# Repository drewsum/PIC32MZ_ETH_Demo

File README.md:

# PIC32MZ_ETH_Demo
A DIY dev board for PIC32MZ EF Ethernet Development

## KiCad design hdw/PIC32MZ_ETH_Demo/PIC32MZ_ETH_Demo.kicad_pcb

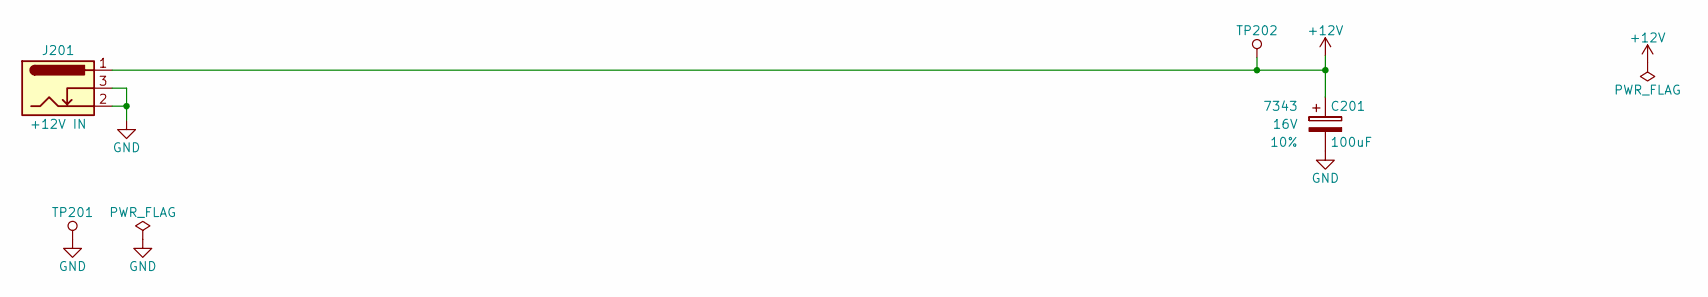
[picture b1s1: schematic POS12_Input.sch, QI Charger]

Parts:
C201: 100uF; CP_Tantalum_Case-X_EIA-7343-43_Reflow; Voltage 16V; Tolerance 10%; Digi-Key PN 718-1102-1-ND
J201: +12V IN; BARREL_JACK
TP201: TP; Pin_Header_Angled_1x01_Pitch2.54mm
TP202: TP; Test_Point

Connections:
+12V: C201.1, J201.1, TP202.1; also elsewhere on the board
GND: C201.2, J201.2, J201.3, TP201.1; also elsewhere on the board

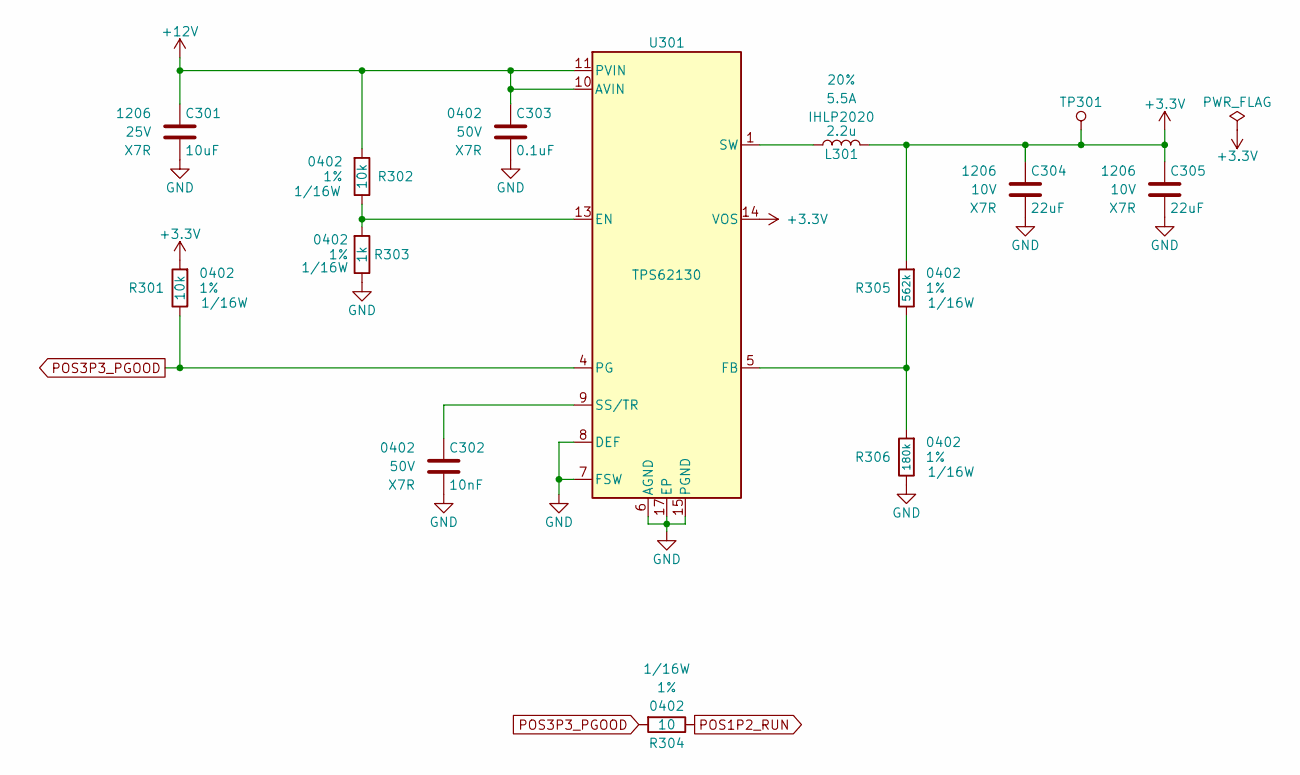
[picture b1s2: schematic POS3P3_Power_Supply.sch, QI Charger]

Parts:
C301: 10uF; C_1206; Voltage 25V; Digi-Key PN 1276-7031-1-ND
C302: 10nF; C_0402; Voltage 50V; Digi-Key PN 490-13295-1-ND
C303: 0.1uF; C_0402; Voltage 50V; Digi-Key PN 490-10701-1-ND
C304, C305: 22uF; C_1206; Voltage 10V; Digi-Key PN 1276-3148-1-ND
L301: 2.2u; L_Vishay_IHLP-2020; Tolerance 20%; Digi-Key PN 541-1236-1-ND
R301, R302: 10k; R_0402; Tolerance 1%; Digi-Key PN RMCF0402FT10K0CT-ND
R303: 1k; R_0402; Tolerance 1%; Digi-Key PN 541-1.00KLCT-ND
R304: 10; R_0402; Tolerance 1%; Digi-Key PN 541-3964-1-ND
R305: 562k; R_0402; Tolerance 1%; Digi-Key PN 541-562KLCT-ND
R306: 180k; R_0402; Tolerance 1%; Digi-Key PN 541-180KLCT-ND
TP301: TP; Test_Point
U301: TPS62130; QFN-16-1EP_3x3mm_Pitch0.5mm; Digi-Key PN 296-37878-1-ND

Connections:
+3V3: C304.1, C305.1, L301.2, R301.1, R305.1, TP301.1, U301.14 (VOS); also elsewhere on the board
+12V: C301.1, C303.1, R302.1, U301.10 (AVIN), U301.11 (PVIN), U301.12 (PVIN); also elsewhere on the board
GND: C301.2, C302.2, C303.2, C304.2, C305.2, R303.2, R306.2, U301.6 (AGND), U301.7 (FSW), U301.8 (DEF), U301.15 (PGND), U301.16 (PGND), U301.17 (EP); also elsewhere on the board
unnamed: C302.1, U301.9 (SS/TR)
unnamed: L301.1, U301.1 (SW), U301.2 (SW), U301.3 (SW)
unnamed: R302.2, R303.1, U301.13 (EN)
unnamed: R305.2, R306.1, U301.5 (FB)
POS1P2_RUN: R304.2; also elsewhere on the board
POS3P3_PGOOD: R301.2, R304.1, U301.4 (PG); also elsewhere on the board

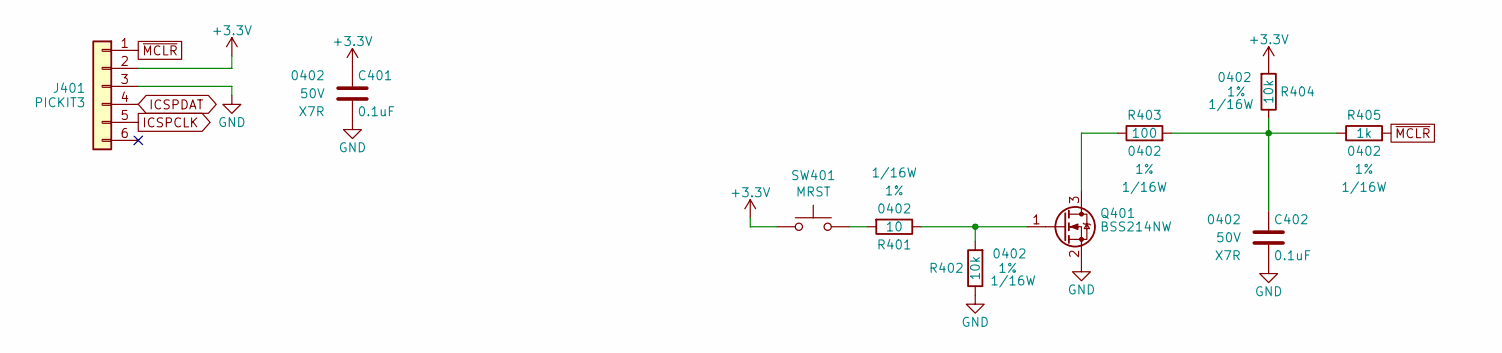
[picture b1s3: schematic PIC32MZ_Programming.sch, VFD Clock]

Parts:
C401, C402: 0.1uF; C_0402; Voltage 50V; Digi-Key PN 490-10701-1-ND
J401: PICKIT3; PICKIT3_Header
Q401: BSS214NW; SOT-323_SC-70; Digi-Key PN BSS214NWH6327XTSA1CT-ND
R401: 10; R_0402; Tolerance 1%; Digi-Key PN 541-3964-1-ND
R402, R404: 10k; R_0402; Tolerance 1%; Digi-Key PN RMCF0402FT10K0CT-ND
R403: 100; R_0402; Tolerance 1%; Digi-Key PN 541-100LCT-ND
R405: 1k; R_0402; Tolerance 1%; Digi-Key PN 541-1.00KLCT-ND
SW401: MRST; SW_PUSH_6mm

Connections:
+3V3: C401.1, J401.2, R404.1, SW401.1; also elsewhere on the board
GND: C401.2, C402.2, J401.3, Q401.2 (S), R402.2; also elsewhere on the board
ICSPCLK: J401.5; also elsewhere on the board
ICSPDAT: J401.4; also elsewhere on the board
unnamed: C402.1, R403.1, R404.2, R405.2
unnamed: Q401.1 (G), R401.2, R402.1
unnamed: Q401.3 (D), R403.2
unnamed: R401.1, SW401.2
~MCLR: J401.1, R405.1; also elsewhere on the board

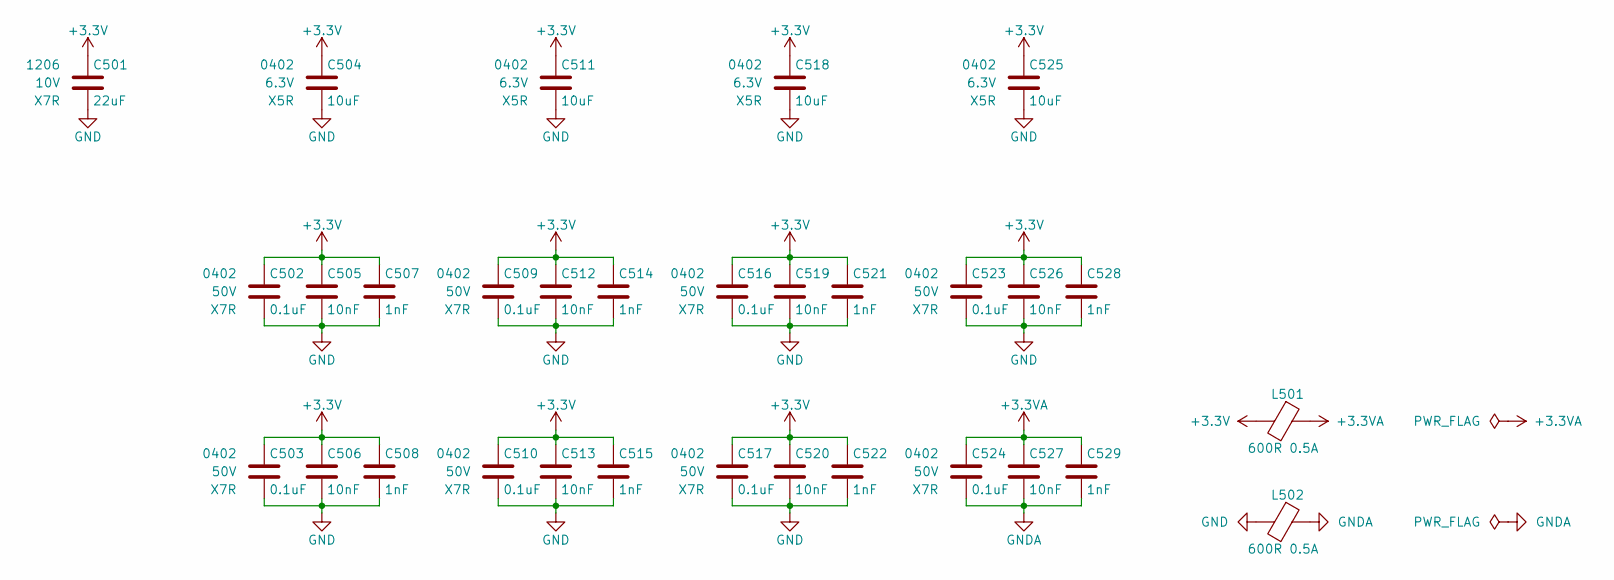
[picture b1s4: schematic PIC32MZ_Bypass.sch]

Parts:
C501: 22uF; C_1206; Voltage 10V; Digi-Key PN 1276-3148-1-ND
C502, C503, C509, C510, C516, C517, C523, C524: 0.1uF; C_0402; Voltage 50V; Digi-Key PN 490-10701-1-ND
C504, C511, C518, C525: 10uF; C_0402; Voltage 6.3V; Digi-Key PN 490-13211-1-ND
C505, C506, C512, C513, C519, C520, C526, C527: 10nF; C_0402; Voltage 50V; Digi-Key PN 490-13295-1-ND
C507, C508, C514, C515, C521, C522, C528, C529: 1nF; C_0402; Voltage 50V; Digi-Key PN 399-1032-1-ND
L501, L502: 600R 0.5A; L_0402; Digi-Key PN 490-5441-1-ND

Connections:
+3.3VA: C524.1, C527.1, C529.1, L501.1; also elsewhere on the board
+3V3: C501.1, C502.1, C503.1, C504.1, C505.1, C506.1, C507.1, C508.1, C509.1, C510.1, C511.1, C512.1, C513.1, C514.1, C515.1, C516.1, C517.1, C518.1, C519.1, C520.1, C521.1, C522.1, C523.1, C525.1, C526.1, C528.1, L501.2; also elsewhere on the board
GND: C501.2, C502.2, C503.2, C504.2, C505.2, C506.2, C507.2, C508.2, C509.2, C510.2, C511.2, C512.2, C513.2, C514.2, C515.2, C516.2, C517.2, C518.2, C519.2, C520.2, C521.2, C522.2, C523.2, C525.2, C526.2, C528.2, L502.2; also elsewhere on the board
GNDA: C524.2, C527.2, C529.2, L502.1; also elsewhere on the board

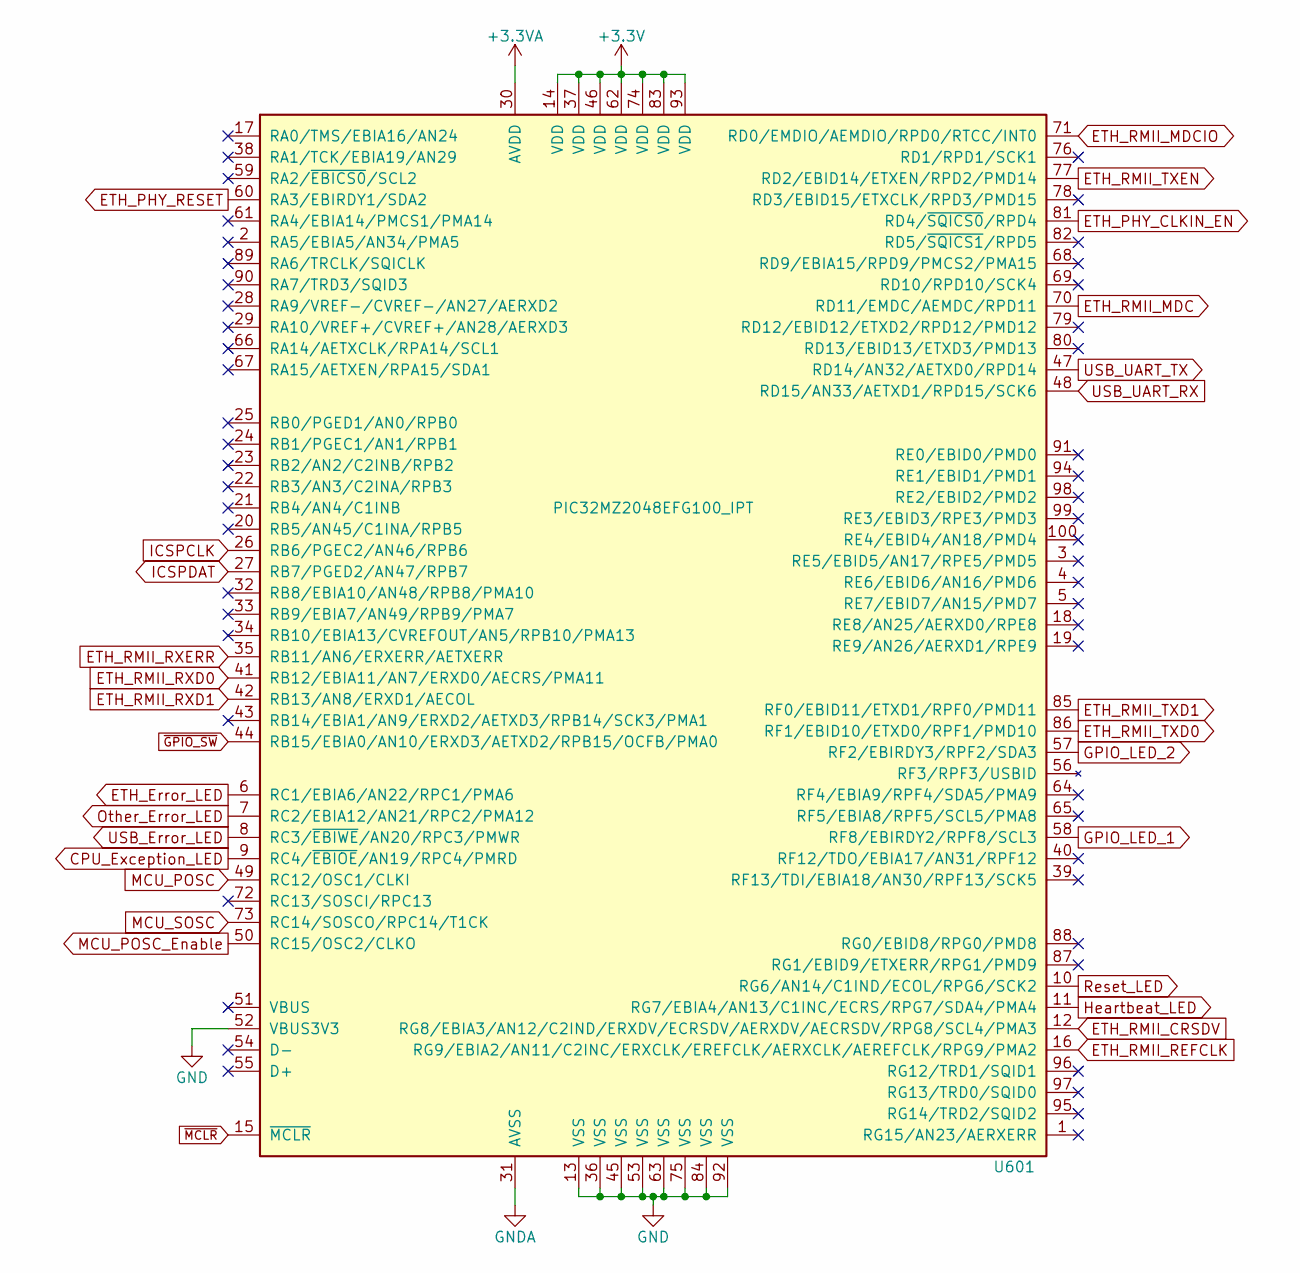
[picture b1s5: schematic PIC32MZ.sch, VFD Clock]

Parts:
U601: PIC32MZ2048EFG100_IPT; TQFP-100_14x14mm_Pitch0.5mm; Digi-Key PN PIC32MZ2048EFG100-I/PT-ND

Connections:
+3.3VA: U601.30 (AVDD); also elsewhere on the board
+3V3: U601.14 (VDD), U601.37 (VDD), U601.46 (VDD), U601.62 (VDD), U601.74 (VDD), U601.83 (VDD), U601.93 (VDD); also elsewhere on the board
CPU_Exception_LED: U601.9 (RC4/~EBIOE~/AN19/RPC4/PMRD); also elsewhere on the board
ETH_Error_LED: U601.6 (RC1/EBIA6/AN22/RPC1/PMA6); also elsewhere on the board
ETH_PHY_CLKIN_EN: U601.81 (RD4/~SQICS0~/RPD4); also elsewhere on the board
ETH_PHY_RESET: U601.60 (RA3/EBIRDY1/SDA2); also elsewhere on the board
ETH_RMII_CRSDV: U601.12 (RG8/EBIA3/AN12/C2IND/ERXDV/ECRSDV/AERXD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); also elsewhere on the board
ETH_RMII_MDC: U601.70 (RD11/EMDC/AEMDC/RPD11); also elsewhere on the board
ETH_RMII_MDCIO: U601.71 (RD0/EMDIO/AEMDIO/RPD0/RTCC/INT0); also elsewhere on the board
ETH_RMII_REFCLK: U601.16 (RG9/EBIA2/AN11/C2INC/ERXCLK/EREFCLK/AER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); also elsewhere on the board
ETH_RMII_RXD0: U601.41 (RB12/EBIA11/AN7/ERXD0/AECRS/PMA11); also elsewhere on the board
ETH_RMII_RXD1: U601.42 (RB13/AN8/ERXD1/AECOL); also elsewhere on the board
ETH_RMII_RXERR: U601.35 (RB11/AN6/ERXERR/AETXERR); also elsewhere on the board
ETH_RMII_TXD0: U601.86 (RF1/EBID10/ETXD0/RPF1/PMD10); also elsewhere on the board
ETH_RMII_TXD1: U601.85 (RF0/EBID11/ETXD1/RPF0/PMD11); also elsewhere on the board
ETH_RMII_TXEN: U601.77 (RD2/EBID14/ETXEN/RPD2/PMD14); also elsewhere on the board
GND: U601.13 (VSS), U601.36 (VSS), U601.45 (VSS), U601.52 (VBUS3V3), U601.53 (VSS), U601.63 (VSS), U601.75 (VSS), U601.84 (VSS), U601.92 (VSS); also elsewhere on the board
GNDA: U601.31 (AVSS); also elsewhere on the board
GPIO_LED_1: U601.58 (RF8/EBIRDY2/RPF8/SCL3); also elsewhere on the board
GPIO_LED_2: U601.57 (RF2/EBIRDY3/RPF2/SDA3); also elsewhere on the board
Heartbeat_LED: U601.11 (RG7/EBIA4/AN13/C1INC/ECRS/RPG7/SDA4/PMA4); also elsewhere on the board
ICSPCLK: U601.26 (RB6/PGEC2/AN46/RPB6); also elsewhere on the board
ICSPDAT: U601.27 (RB7/PGED2/AN47/RPB7); also elsewhere on the board
MCU_POSC: U601.49 (RC12/OSC1/CLKI); also elsewhere on the board
MCU_POSC_Enable: U601.50 (RC15/OSC2/CLKO); also elsewhere on the board
MCU_SOSC: U601.73 (RC14/SOSCO/RPC14/T1CK); also elsewhere on the board
Other_Error_LED: U601.7 (RC2/EBIA12/AN21/RPC2/PMA12); also elsewhere on the board
Reset_LED: U601.10 (RG6/AN14/C1IND/ECOL/RPG6/SCK2); also elsewhere on the board
USB_Error_LED: U601.8 (RC3/~EBIWE~/AN20/RPC3/PMWR); also elsewhere on the board
USB_UART_RX: U601.48 (RD15/AN33/AETXD1/RPD15/SCK6); also elsewhere on the board
USB_UART_TX: U601.47 (RD14/AN32/AETXD0/RPD14); also elsewhere on the board
~GPIO_SW: U601.44 (RB15/EBIA0/AN10/ERXD3/AETXD2/RPB15/OCFB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); also elsewhere on the board
~MCLR: U601.15 (~MCLR~); also elsewhere on the board

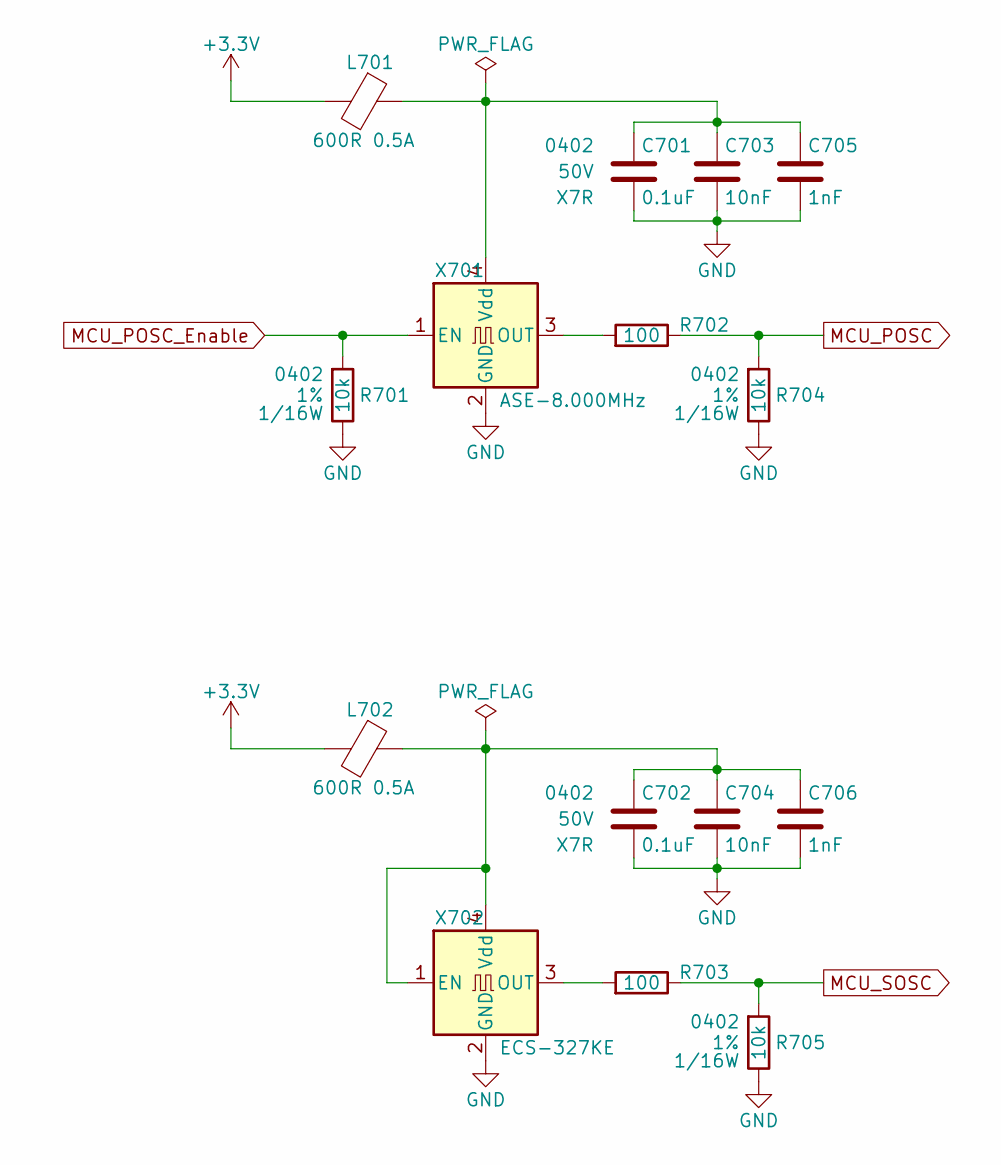
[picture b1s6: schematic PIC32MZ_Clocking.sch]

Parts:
C701, C702: 0.1uF; C_0402; Voltage 50V; Digi-Key PN 490-10701-1-ND
C703, C704: 10nF; C_0402; Voltage 50V; Digi-Key PN 490-13295-1-ND
C705, C706: 1nF; C_0402; Voltage 50V; Digi-Key PN 399-1032-1-ND
L701, L702: 600R 0.5A; L_0402; Digi-Key PN 490-5441-1-ND
R701, R704, R705: 10k; R_0402; Tolerance 1%; Digi-Key PN RMCF0402FT10K0CT-ND
R702, R703: 100; R_0402; Tolerance 1%; Digi-Key PN 541-100LCT-ND
X701: ASE-8.000MHz; Oscillator_SMD_Abracon_ASE-4Pin_3.2x2.5mm; Digi-Key PN 535-9558-1-ND
X702: ECS-327KE; Digi-Key PN XC1751CT-ND

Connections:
+3V3: L701.2, L702.2; also elsewhere on the board
GND: C701.2, C702.2, C703.2, C704.2, C705.2, C706.2, R701.2, R704.2, R705.2, X701.2 (GND), X702.2 (GND); also elsewhere on the board
MCU_POSC: R702.2, R704.1; also elsewhere on the board
MCU_POSC_Enable: R701.1, X701.1 (EN); also elsewhere on the board
MCU_SOSC: R703.2, R705.1; also elsewhere on the board
unnamed: C701.1, C703.1, C705.1, L701.1, X701.4 (Vdd)
unnamed: C702.1, C704.1, C706.1, L702.1, X702.1 (EN), X702.4 (Vdd)
unnamed: R702.1, X701.3 (OUT)
unnamed: R703.1, X702.3 (OUT)

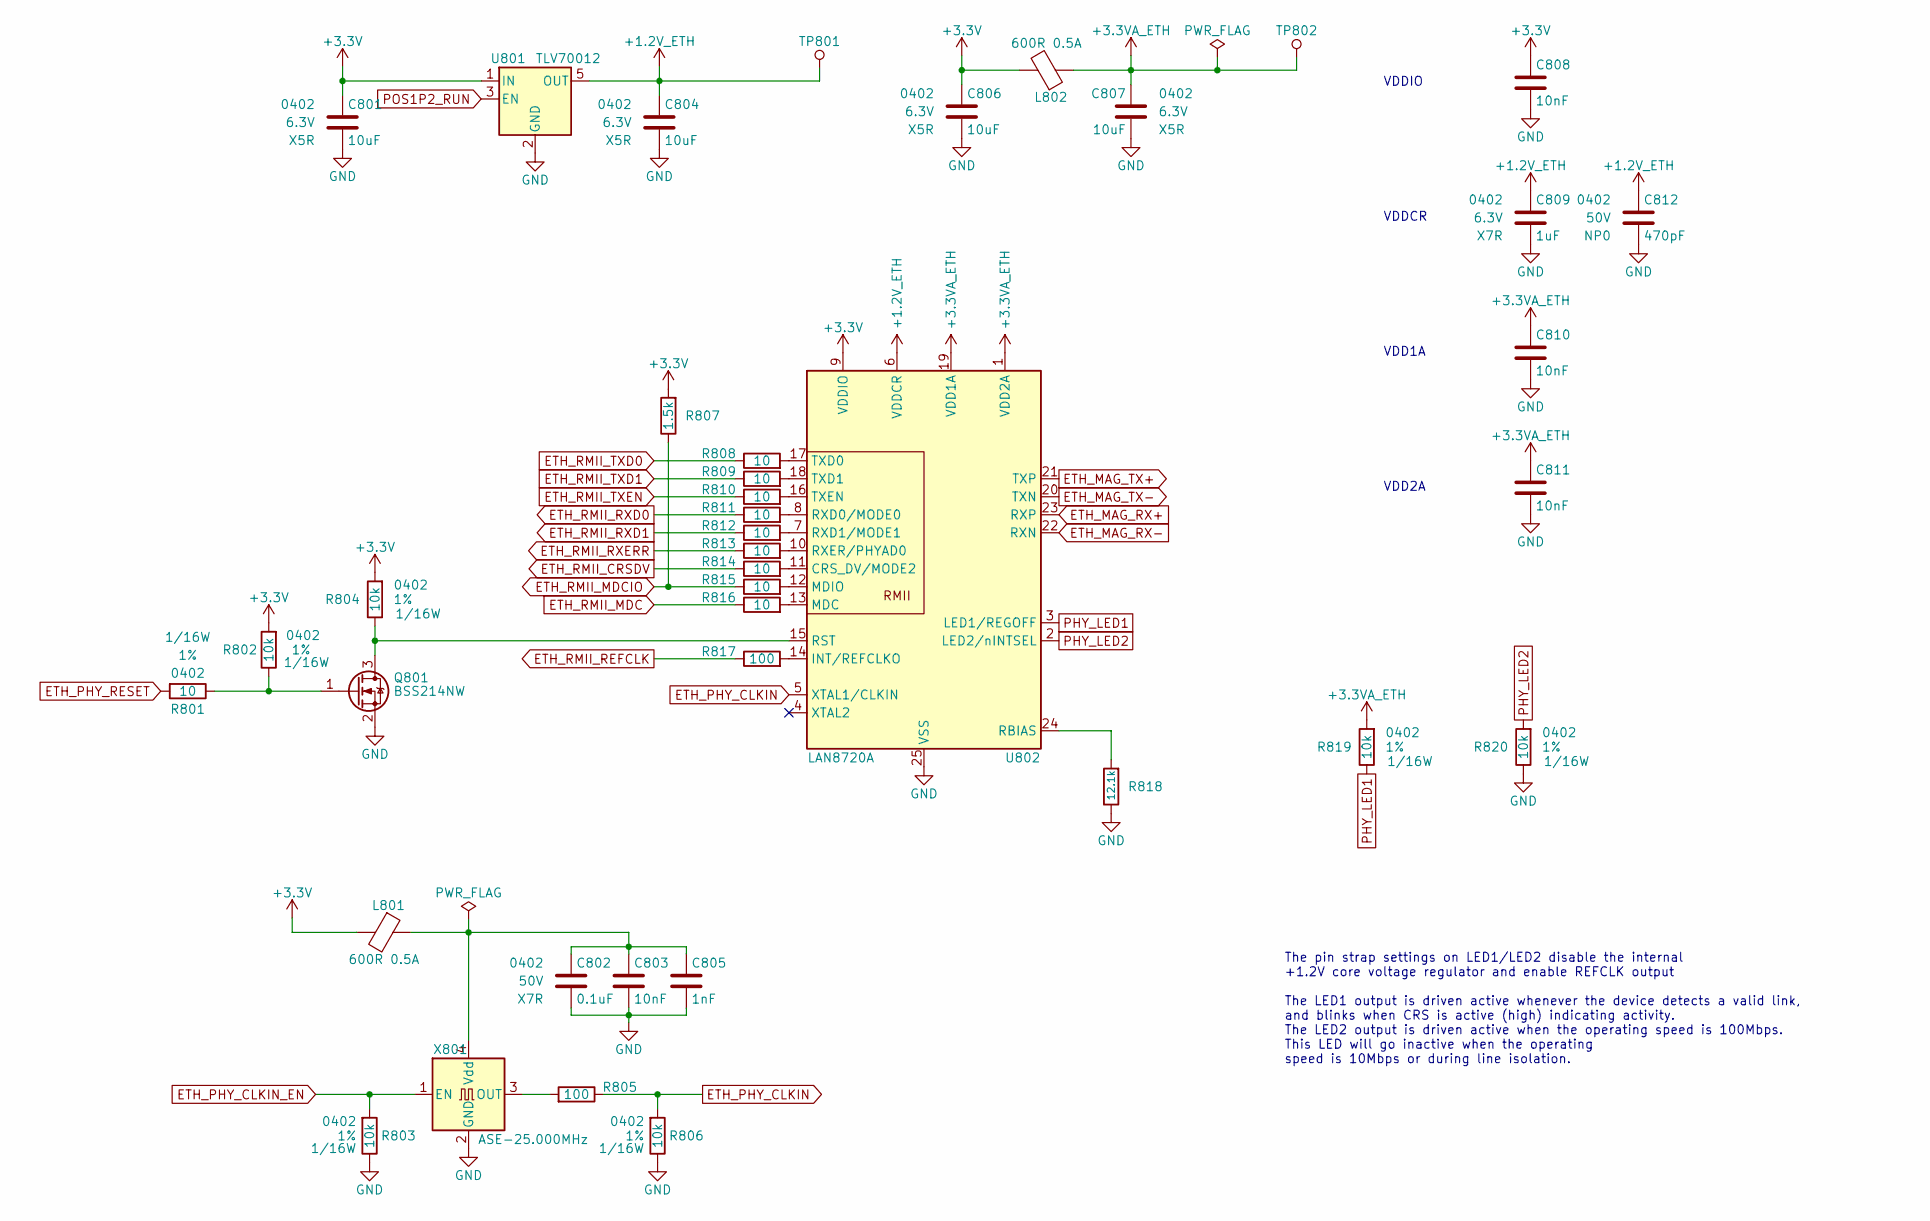
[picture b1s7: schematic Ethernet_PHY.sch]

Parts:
C801, C804, C806, C807: 10uF; C_0402; Voltage 6.3V; Digi-Key PN 490-13211-1-ND
C802: 0.1uF; C_0402; Voltage 50V; Digi-Key PN 490-10701-1-ND
C803, C808, C810, C811: 10nF; C_0402; Voltage 50V; Digi-Key PN 490-13295-1-ND
C805: 1nF; C_0402; Voltage 50V; Digi-Key PN 399-1032-1-ND
C809: 1uF; C_0402; Voltage 6.3V; Digi-Key PN 490-9665-1-ND
C812: 470pF; C_0402; Voltage 50V; Digi-Key PN 399-1025-1-ND
L801, L802: 600R 0.5A; L_0402; Digi-Key PN 490-5441-1-ND
Q801: BSS214NW; SOT-323_SC-70; Digi-Key PN BSS214NWH6327XTSA1CT-ND
R801, R808, R809, R810, R811, R812, R813, R814, R815, R816: 10; R_0402; Tolerance 1%; Digi-Key PN 541-3964-1-ND
R802, R803, R804, R806, R819, R820: 10k; R_0402; Tolerance 1%; Digi-Key PN RMCF0402FT10K0CT-ND
R805, R817: 100; R_0402; Tolerance 1%; Digi-Key PN 541-100LCT-ND
R807: 1.5k; R_0402; Tolerance 1%; Digi-Key PN 541-1.50KLCT-ND
R818: 12.1k; R_0402; Tolerance 1%; Digi-Key PN 541-CRCW040212K1FKTDCT-ND
TP801, TP802: TP_Pad; Test_Point
U801: TLV70012; SOT-353_SC-70-5; Digi-Key PN 296-27438-1-ND
U802: LAN8720A; QFN-24-1EP_4x4mm_P0.5mm_EP2.6x2.6mm; Digi-Key PN LAN8720A-CP-CT-ND
X801: ASE-25.000MHz; Oscillator_SMD_Abracon_ASE-4Pin_3.2x2.5mm; Digi-Key PN 535-13429-1-ND

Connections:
+1.2V_ETH: C804.1, C809.1, C812.1, TP801.1, U801.5 (OUT), U802.6 (VDDCR)
+3.3VA_ETH: C807.1, C810.1, C811.1, L802.1, R819.1, TP802.1, U802.1 (VDD2A), U802.19 (VDD1A); also elsewhere on the board
+3V3: C801.1, C806.1, C808.1, L801.2, L802.2, R802.1, R804.1, R807.1, U801.1 (IN), U802.9 (VDDIO); also elsewhere on the board
ETH_MAG_RX+: U802.23 (RXP); also elsewhere on the board
ETH_MAG_RX-: U802.22 (RXN); also elsewhere on the board
ETH_MAG_TX+: U802.21 (TXP); also elsewhere on the board
ETH_MAG_TX-: U802.20 (TXN); also elsewhere on the board
ETH_PHY_CLKIN: R805.2, R806.1, U802.5 (XTAL1/CLKIN)
ETH_PHY_CLKIN_EN: R803.1, X801.1 (EN); also elsewhere on the board
ETH_PHY_RESET: R801.1; also elsewhere on the board
ETH_RMII_CRSDV: R814.2; also elsewhere on the board
ETH_RMII_MDC: R816.2; also elsewhere on the board
ETH_RMII_MDCIO: R807.2, R815.2; also elsewhere on the board
ETH_RMII_REFCLK: R817.2; also elsewhere on the board
ETH_RMII_RXD0: R811.2; also elsewhere on the board
ETH_RMII_RXD1: R812.2; also elsewhere on the board
ETH_RMII_RXERR: R813.2; also elsewhere on the board
ETH_RMII_TXD0: R808.2; also elsewhere on the board
ETH_RMII_TXD1: R809.2; also elsewhere on the board
ETH_RMII_TXEN: R810.2; also elsewhere on the board
GND: C801.2, C802.2, C803.2, C804.2, C805.2, C806.2, C807.2, C808.2, C809.2, C810.2, C811.2, C812.2, Q801.2 (S), R803.2, R806.2, R818.2, R820.2, U801.2 (GND), U802.25 (VSS), X801.2 (GND); also elsewhere on the board
unnamed: C802.1, C803.1, C805.1, L801.1, X801.4 (Vdd)
unnamed: Q801.1 (G), R801.2, R802.2
unnamed: Q801.3 (D), R804.2, U802.15 (RST)
unnamed: R805.1, X801.3 (OUT)
unnamed: R808.1, U802.17 (TXD0)
unnamed: R809.1, U802.18 (TXD1)
unnamed: R810.1, U802.16 (TXEN)
unnamed: R811.1, U802.8 (RXD0/MODE0)
unnamed: R812.1, U802.7 (RXD1/MODE1)
unnamed: R813.1, U802.10 (RXER/PHYAD0)
unnamed: R814.1, U802.11 (CRS_DV/MODE2)
unnamed: R815.1, U802.12 (MDIO)
unnamed: R816.1, U802.13 (MDC)
unnamed: R817.1, U802.14 (INT/REFCLKO)
unnamed: R818.1, U802.24 (RBIAS)
PHY_LED1: R819.2, U802.3 (LED1/REGOFF); also elsewhere on the board
PHY_LED2: R820.1, U802.2 (LED2/nINTSEL); also elsewhere on the board
POS1P2_RUN: U801.3 (EN); also elsewhere on the board

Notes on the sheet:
The pin strap settings on LED1/LED2 disable the internal +1.2V core voltage regulator and enable REFCLK output The LED1 output is driven active whenever the device detects a valid link, and blinks when CRS is active (high) indicating activity. The LED2 output is driven active when the operating spe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
VDDCR
VDDIO
VDD1A
VDD2A

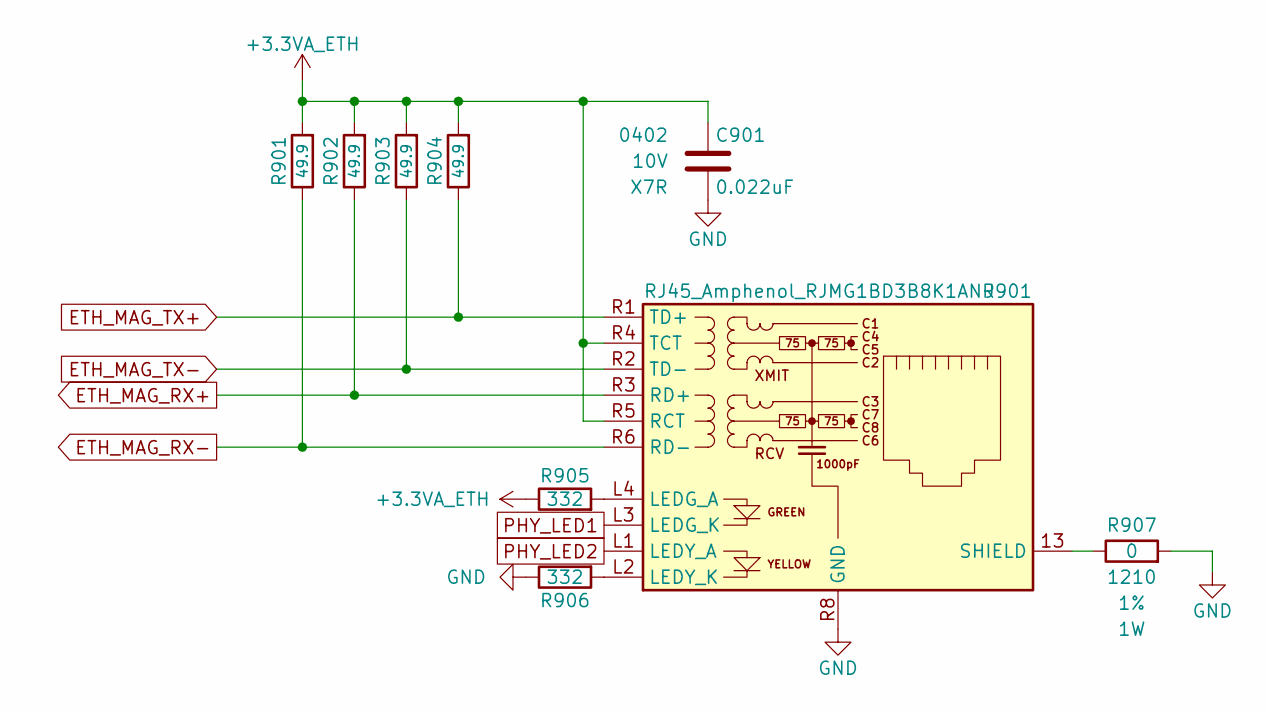
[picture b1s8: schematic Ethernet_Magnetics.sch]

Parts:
C901: 0.022uF; C_0402; Voltage 10V; Digi-Key PN 311-3793-1-ND
J901: RJ45_Amphenol_RJMG1BD3B8K1ANR; Digi-Key PN RJMG1BD3B8K1ANR-ND
R901, R902, R903, R904: 49.9; R_0402; Tolerance 1%; Digi-Key PN 541-3967-1-ND
R905, R906: 332; R_0402; Tolerance 1%; Digi-Key PN 541-332LCT-ND
R907: 0; R_1210; Tolerance 1%; Digi-Key PN RMCF1210ZT0R00CT-ND

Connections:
+3.3VA_ETH: C901.1, J901.R4 (TCT), J901.R5 (RCT), R901.1, R902.1, R903.1, R904.1, R905.2; also elsewhere on the board
ETH_MAG_RX+: J901.R3 (RD+), R902.2; also elsewhere on the board
ETH_MAG_RX-: J901.R6 (RD-), R901.2; also elsewhere on the board
ETH_MAG_TX+: J901.R1 (TD+), R904.2; also elsewhere on the board
ETH_MAG_TX-: J901.R2 (TD-), R903.2; also elsewhere on the board
GND: C901.2, J901.R8 (GND), R906.2, R907.1; also elsewhere on the board
unnamed: J901.13 (SHIELD), R907.2
unnamed: J901.L2 (LEDY_K), R906.1
unnamed: J901.L4 (LEDG_A), R905.1
PHY_LED1: J901.L3 (LEDG_K); also elsewhere on the board
PHY_LED2: J901.L1 (LEDY_A); also elsewhere on the board

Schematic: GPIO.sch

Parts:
C1001, C1002, C1003: 0.1uF; C_0402; Voltage 50V; Digi-Key PN 490-10701-1-ND
D1001, D1002: Green; LED_0402; Digi-Key PN 1497-1219-1-ND
R1001, R1003, R1005: 10k; R_0402; Tolerance 1%; Digi-Key PN RMCF0402FT10K0CT-ND
R1002, R1004: 1k; R_0402; Tolerance 1%; Digi-Key PN 541-1.00KLCT-ND
SW1001: GPIO_SW; SW_PUSH_6mm
U1001, U1003: 74LVC1G97; SOT-363_SC-70-6; Digi-Key PN 296-15582-1-ND
U1002: MAX6816; SOT-143; Digi-Key PN MAX6816EUS+TCT-ND

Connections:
+3V3: C1001.1, C1002.1, C1003.1, R1002.1, R1004.1, R1005.1, U1001.1 (VCC), U1001.5 (VCC), U1002.4 (VCC), U1003.1 (VCC), U1003.5 (VCC); also elsewhere on the board
GND: C1001.2, C1002.2, C1003.2, R1001.2, R1003.2, SW1001.1, U1001.2 (GND), U1001.3 (GND), U1002.1 (GND), U1003.2 (GND), U1003.3 (GND); also elsewhere on the board
GPIO_LED_1: R1001.1, U1001.6; also elsewhere on the board
GPIO_LED_2: R1003.1, U1003.6; also elsewhere on the board
unnamed: D1001.1 (K), U1001.4
unnamed: D1001.2 (A), R1002.2
unnamed: D1002.1 (K), U1003.4
unnamed: D1002.2 (A), R1004.2
unnamed: SW1001.2, U1002.2 (IN)
~GPIO_SW: R1005.2, U1002.3 (OUT); also elsewhere on the board

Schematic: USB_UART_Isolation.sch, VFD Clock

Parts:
C1101, C1103: 0.1uF; C_0402; Voltage 50V; Digi-Key PN 490-10701-1-ND
C1102: 0.56uF; C_2220; Voltage 250VAC; Digi-Key PN 565-4707-1-ND
R1101, R1102, R1103, R1104: 10k; R_0402; Tolerance 1%; Digi-Key PN RMCF0402FT10K0CT-ND
U1101: ISO7321C; SOIC-8_3.9x4.9mm_Pitch1.27mm; Digi-Key PN 296-42102-1-ND

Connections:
+3V3: C1101.1, R1101.1, R1102.1, U1101.1 (VCC1); also elsewhere on the board
+5V_USB: C1103.1, R1103.1, R1104.1, U1101.8 (VCC2); also elsewhere on the board
GND: C1101.2, C1102.1, U1101.4 (GND1); also elsewhere on the board
GND_USB: C1102.2, C1103.2, U1101.5 (GND2); also elsewhere on the board
USB_UART_RX: R1101.2, U1101.2 (OUTA); also elsewhere on the board
USB_UART_RX_ISO: R1104.2, U1101.7 (INA); also elsewhere on the board
USB_UART_TX: R1102.2, U1101.3 (INB); also elsewhere on the board
USB_UART_TX_ISO: R1103.2, U1101.6 (OUTB); also elsewhere on the board

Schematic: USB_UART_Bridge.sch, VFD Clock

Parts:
C1201, C1202, C1203, C1204, C1206, C1207, C1210: 0.1uF; C_0402; Voltage 50V; Digi-Key PN 490-10701-1-ND
C1205: 4.7uF; C_0805; Voltage 10V; Digi-Key PN 1276-2972-1-ND
C1208, C1209: 47pF; C_0402; Voltage 50V; Digi-Key PN 399-17558-1-ND
D1201: Yellow; LED_0402; Digi-Key PN 1497-1389-1-ND
DOC1201: COM_Port_Settings
J1201: USB_B_Mini; USB_Mini-B; Digi-Key PN 732-2109-1-ND
L1201, L1202: 600R 0.5A; L_0402; Digi-Key PN 490-5441-1-ND
R1201, R1205: 10k; R_0402; Tolerance 1%; Digi-Key PN RMCF0402FT10K0CT-ND
R1202: 487k; R_0402; Tolerance 1%; Digi-Key PN RMCF0402FT487KCT-ND
R1203: 6.04k; R_0402; Tolerance 1%; Digi-Key PN 541-4067-1-ND
R1204: 40.2k; R_0402; Tolerance 1%; Digi-Key PN 541-4097-1-ND
R1206, R1207: 27; R_0402; Tolerance 1%; Digi-Key PN 541-4082-1-ND
R1208: 1k; R_0402; Tolerance 1%; Digi-Key PN 541-1.00KLCT-ND
U1201: TLV6700; SOT-23-6; Digi-Key PN 296-51696-1-ND
U1202: FT234XD; DFN-12-1EP_3x3mm_Pitch0.45mm; Digi-Key PN 768-1178-1-ND
U1203: TPD3S014DBVR; SOT-23-6; Digi-Key PN 296-38835-1-ND

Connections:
+5V_USB: C1202.1, C1203.1, C1204.1, C1205.1, C1206.1, R1201.1, R1202.1, R1205.1, R1208.1, U1201.5 (Vs), U1202.4 (VCC), U1202.9 (VCCIO), U1203.4 (OUT); also elsewhere on the board
/USB UART Bridge/BRIDGE_USB+: R1206.2, U1202.12 (USBDP)
/USB UART Bridge/BRIDGE_USB-: R1207.2, U1202.1 (USBDM)
/USB UART Bridge/CONN_USB+: C1208.1, J1201.3 (D+), R1206.1, U1203.6 (D1)
/USB UART Bridge/CONN_USB-: C1209.1, J1201.2 (D-), R1207.1, U1203.5 (D2)
GND_USB: C1201.2, C1202.2, C1203.2, C1204.2, C1205.2, C1206.2, C1207.2, C1208.2, C1209.2, C1210.2, J1201.5 (GND), L1202.1, R1204.2, U1201.2 (GND), U1202.5 (GND), U1202.13 (GND), U1203.2 (GND); also elsewhere on the board
unnamed: C1201.1, R1201.2, U1202.2 (~RESET)
unnamed: C1207.1, U1202.3 (3V3OUT)
unnamed: C1210.1, L1201.2, U1203.1 (EN), U1203.3 (IN)
unnamed: D1201.2 (A), R1208.2
unnamed: J1201.1 (VBUS), L1201.1
unnamed: J1201.6 (Shield), L1202.2
unnamed: R1202.2, R1203.1, U1201.3 (+INA)
unnamed: R1203.2, R1204.1, U1201.4 (-INB)
POS5_USB_PGOOD: R1205.2, U1201.1 (OUTA), U1201.6 (OUTB); also elsewhere on the board
USB_UART_RX_ISO: U1202.7 (TXD); also elsewhere on the board
USB_UART_TX_ISO: U1202.10 (RXD); also elsewhere on the board
~USB_ACTIVE: D1201.1 (K), U1202.6 (CBUS0)

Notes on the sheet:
11. USB UART Bridge

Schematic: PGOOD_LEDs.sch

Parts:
C1301, C1302: 0.1uF; C_0402; Voltage 50V; Digi-Key PN 490-10701-1-ND
D1301, D1302: Green; LED_0402; Digi-Key PN 1497-1219-1-ND
R1301, R1302: 1k; R_0402; Tolerance 1%; Digi-Key PN 541-1.00KLCT-ND
U1301, U1302: 74LVC1G97; SOT-363_SC-70-6; Digi-Key PN 296-15582-1-ND

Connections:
+3V3: C1301.1, R1301.1, U1301.1 (VCC), U1301.5 (VCC); also elsewhere on the board
+5V_USB: C1302.1, R1302.1, U1302.1 (VCC), U1302.5 (VCC); also elsewhere on the board
GND: C1301.2, U1301.2 (GND), U1301.3 (GND); also elsewhere on the board
GND_USB: C1302.2, U1302.2 (GND), U1302.3 (GND); also elsewhere on the board
unnamed: D1301.1 (K), U1301.4
unnamed: D1301.2 (A), R1301.2
unnamed: D1302.1 (K), U1302.4
unnamed: D1302.2 (A), R1302.2
POS3P3_PGOOD: U1301.6; also elsewhere on the board
POS5_USB_PGOOD: U1302.6; also elsewhere on the board

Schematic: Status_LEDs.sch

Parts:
C1401, C1402, C1403, C1404, C1405, C1406: 0.1uF; C_0402; Voltage 50V; Digi-Key PN 490-10701-1-ND
D1401: Green; LED_0402; Digi-Key PN 1497-1219-1-ND
D1402, D1403, D1404, D1405, D1406: Red; LED_0402; Digi-Key PN 1497-1174-1-ND
R1401, R1403, R1404, R1407, R1408, R1411: 10k; R_0402; Tolerance 1%; Digi-Key PN RMCF0402FT10K0CT-ND
R1402, R1405, R1406, R1409, R1410, R1412: 1k; R_0402; Tolerance 1%; Digi-Key PN 541-1.00KLCT-ND
U1401, U1402, U1403, U1404, U1405, U1406: 74LVC1G97; SOT-363_SC-70-6; Digi-Key PN 296-15582-1-ND

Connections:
+3V3: C1401.1, C1402.1, C1403.1, C1404.1, C1405.1, C1406.1, R1402.1, R1403.1, R1405.1, R1406.1, R1409.1, R1410.1, R1412.1, U1401.1 (VCC), U1401.5 (VCC), U1402.1 (VCC), U1402.5 (VCC), U1403.1 (VCC), U1403.5 (VCC), U1404.1 (VCC), U1404.5 (VCC), U1405.1 (VCC), U1405.5 (VCC), U1406.1 (VCC), U1406.5 (VCC); also elsewhere on the board
CPU_Exception_LED: R1404.1, U1403.6; also elsewhere on the board
ETH_Error_LED: R1411.1, U1406.6; also elsewhere on the board
GND: C1401.2, C1402.2, C1403.2, C1404.2, C1405.2, C1406.2, R1401.2, R1404.2, R1407.2, R1408.2, R1411.2, U1401.2 (GND), U1401.3 (GND), U1402.2 (GND), U1402.3 (GND), U1403.2 (GND), U1403.3 (GND), U1404.2 (GND), U1404.3 (GND), U1405.2 (GND), U1405.3 (GND), U1406.2 (GND), U1406.3 (GND); also elsewhere on the board
Heartbeat_LED: R1401.1, U1401.6; also elsewhere on the board
unnamed: D1401.1 (K), U1401.4
unnamed: D1401.2 (A), R1402.2
unnamed: D1402.1 (K), U1402.4
unnamed: D1402.2 (A), R1405.2
unnamed: D1403.1 (K), U1403.4
unnamed: D1403.2 (A), R1406.2
unnamed: D1404.1 (K), U1404.4
unnamed: D1404.2 (A), R1409.2
unnamed: D1405.1 (K), U1405.4
unnamed: D1405.2 (A), R1410.2
unnamed: D1406.1 (K), U1406.4
unnamed: D1406.2 (A), R1412.2
Other_Error_LED: R1408.1, U1405.6; also elsewhere on the board
Reset_LED: R1403.2, U1402.6; also elsewhere on the board
USB_Error_LED: R1407.1, U1404.6; also elsewhere on the board

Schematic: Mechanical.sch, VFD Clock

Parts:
H1501, H1502, H1503, H1504, H1505: MountingHole; MountingHole_3mm
MK1501, MK1502, MK1505, MK1506, MK1509: Standoff; Digi-Key PN 1772-2080-ND
MK1503, MK1504, MK1507, MK1508, MK1511: Screw; Digi-Key PN 36-9900-ND
